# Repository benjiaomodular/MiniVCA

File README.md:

# MiniVCA

An LM13700 VCA based on Juanito Moore's design. Check out his original circuit here: https://drive.google.com/file/d/1J9KlYRYUHS_VxaGyPMjCsaK7Lp2Q8HFu/view

# Versions

## 1.2 (Unverified)
- Changed mounting hole spacing to Doepfer standards.
- Export separate gerber files for each board instead of mousebites.

## 1.1
- Minor corrections from initial print.
- Updated front panel graphics to my new standard styles.

## 1.0
Initial design.

### Issues
- Socket for LM13700 was wrong. Used 10.16mm instead of 7.62mm width. Can be remedied by bending the IC's pins wide. Verified to work.
- No silk screen label for pots.

### Issues
- Replaced footprint for LM13700 with correct one.
- Added silk screen labels for the pots.
- Move all front panel text to F.Mask layer.

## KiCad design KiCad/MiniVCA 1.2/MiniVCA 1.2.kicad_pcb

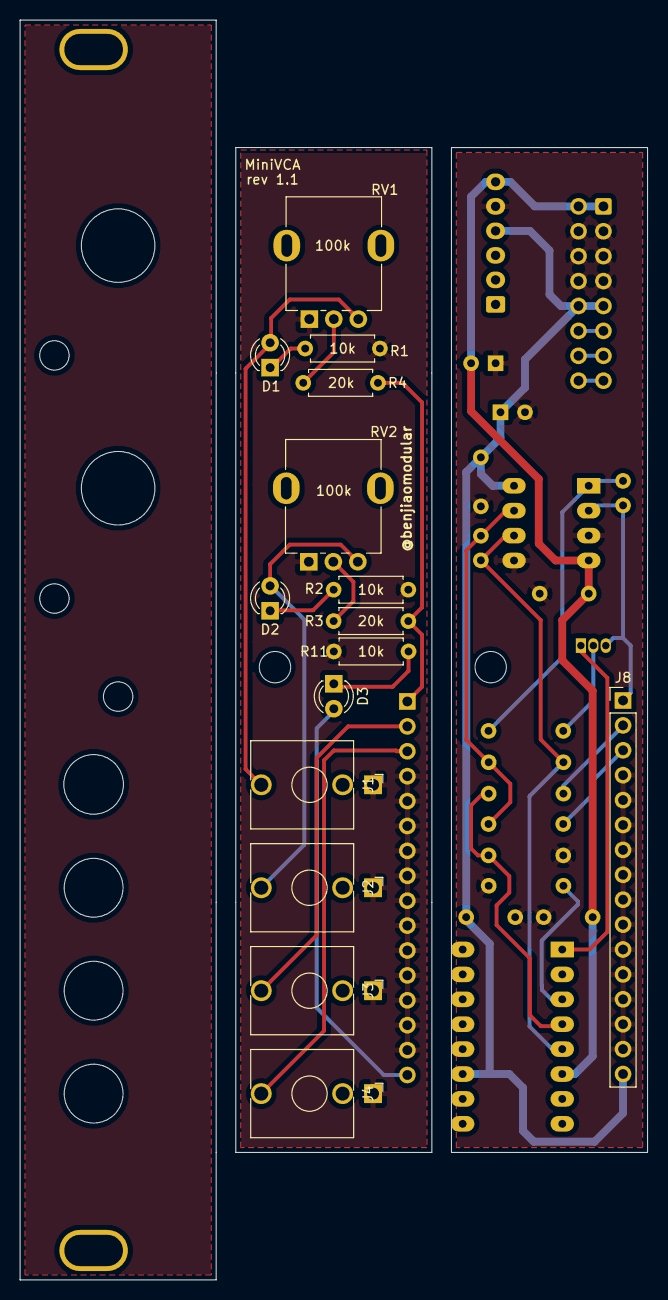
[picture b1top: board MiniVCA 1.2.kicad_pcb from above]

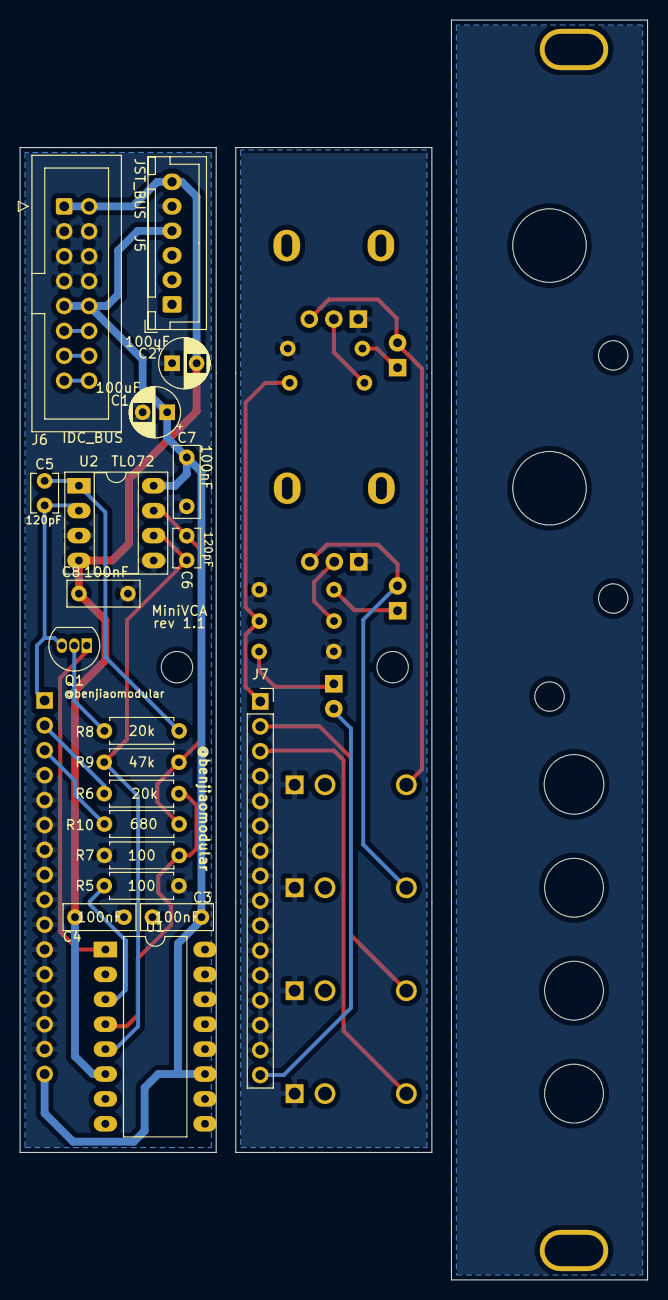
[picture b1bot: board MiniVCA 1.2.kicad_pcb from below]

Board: 2 copper layers, 64.0 x 128.5 mm, 35 parts (20 on the bottom side), 28 nets.

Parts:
C1, C2: 100uF; CP_Radial_D5.0mm_P2.50mm
C3, C4, C7, C8: 100nF; C_Rect_L7.2mm_W2.5mm_P5.00mm_FKS2_FKP2_MKS2_MKP2
C5, C6: 120pF; C_Disc_D3.8mm_W2.6mm_P2.50mm
D1, D2, D3: LED; LED_D3.0mm
J1: CV_2; AudioJack_3.5mm
J2: CV_1; AudioJack_3.5mm
J3: AudioIn; AudioJack_3.5mm
J4: AudioOut; AudioJack_3.5mm
J5: JST_BUS; JST_XH_B6B-XH-A_1x06_P2.50mm_Vertical
J6: IDC_BUS; IDC-Header_2x08_P2.54mm_Vertical
J7: BOARD1_HEADERS; PinSocket_1x16_P2.54mm_Vertical
J8: BOARD2_HEADERS; PinHeader_1x16_P2.54mm_Vertical
Q1: BC559; TO-92_Inline
R1, R2, R11: 10k; R_Axial_DIN0207_L6.3mm_D2.5mm_P7.62mm_Horizontal
R3, R4, R6, R8: 20k; R_Axial_DIN0207_L6.3mm_D2.5mm_P7.62mm_Horizontal
R5, R7: 100; R_Axial_DIN0207_L6.3mm_D2.5mm_P7.62mm_Horizontal
R9: 47k; R_Axial_DIN0207_L6.3mm_D2.5mm_P7.62mm_Horizontal
R10: 680; R_Axial_DIN0207_L6.3mm_D2.5mm_P7.62mm_Horizontal
RV1, RV2: 100k; Potentiometer_RV09
U1: LM13700; DIP-16_W10.16mm_LongPads
U2: TL072; DIP-8_W7.62mm_Socket_LongPads

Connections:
-12V: C2.2, C4.2, C8.2, J5.6, J6.1, J6.2, U1.6, U2.4
B1_1: J7.1, R3.1, R4.1
B1_2: J3.T, J7.2
B1_3: J4.T, J7.3
B1_12V: D3.2, J7.16
B2_1: C5.2, J8.1, Q1.3, U2.2
B2_2: J8.2, R6.2
B2_3: J8.3, R10.1
B2_12V: C1.1, C3.2, C7.2, J5.4, J6.9, J6.10, J8.16, U1.11, U2.8
GND1: J1.S, J2.S, J3.S, J4.S, J7.4, J7.5, J7.6, J7.7, J7.8, J7.9, J7.10, J7.11, J7.12, J7.13, J7.14, J7.15, R1.1, R2.1, R11.1, RV1.1, RV2.1
GND2: C1.2, C2.1, C3.1, C4.1, C7.1, C8.1, J5.5, J6.3, J6.4, J6.5, J6.6, J6.7, J6.8, J8.4, J8.5, J8.6, J8.7, J8.8, J8.9, J8.10, J8.11, J8.12, J8.13, J8.14, J8.15, R5.1, R7.1, U2.3, U2.5
unnamed: C5.1, R8.2, U2.1
unnamed: C6.1, R9.1, R10.2, U2.7
unnamed: C6.2, R9.2, U1.5, U2.6
unnamed: D1.1, R1.2
unnamed: D1.2, J1.T, RV1.3
unnamed: D2.1, R2.2
unnamed: D2.2, J2.T, RV2.3
unnamed: D3.1, R11.2
unnamed: J6.11, J6.12
unnamed: J6.13, J6.14
unnamed: J6.15, J6.16
unnamed: Q1.1, U1.1
unnamed: Q1.2, R8.1
unnamed: R3.2, RV2.2
unnamed: R4.2, RV1.2
unnamed: R5.2, U1.3
unnamed: R6.1, R7.2, U1.4

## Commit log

2021-12-08 Added version 1.0 schematic
2021-12-08 Added gitignore
2021-12-08 Added 4hp pcb
2021-12-22 Added rev1.1
2021-12-27 Added files for version 1.1
2022-01-17 Fixed front panel print
2022-02-17 Added pdf for v1.1 schematics
2022-05-12 Added v1.2
